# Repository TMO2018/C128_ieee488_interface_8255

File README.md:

# C128_ieee488_interface_8255
ieee488-Interface for the C128 using the expansions-port with PIA 8255 published in the 64er Sonderheft 10

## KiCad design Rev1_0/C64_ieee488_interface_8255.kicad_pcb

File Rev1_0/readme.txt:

Kicad 5.0.1

rev 1.0
- PCBWay
- Expansionsport- und ieee488-Platinenanschluss: beidseitig 45 Grad anfasen, 0,5mm tief

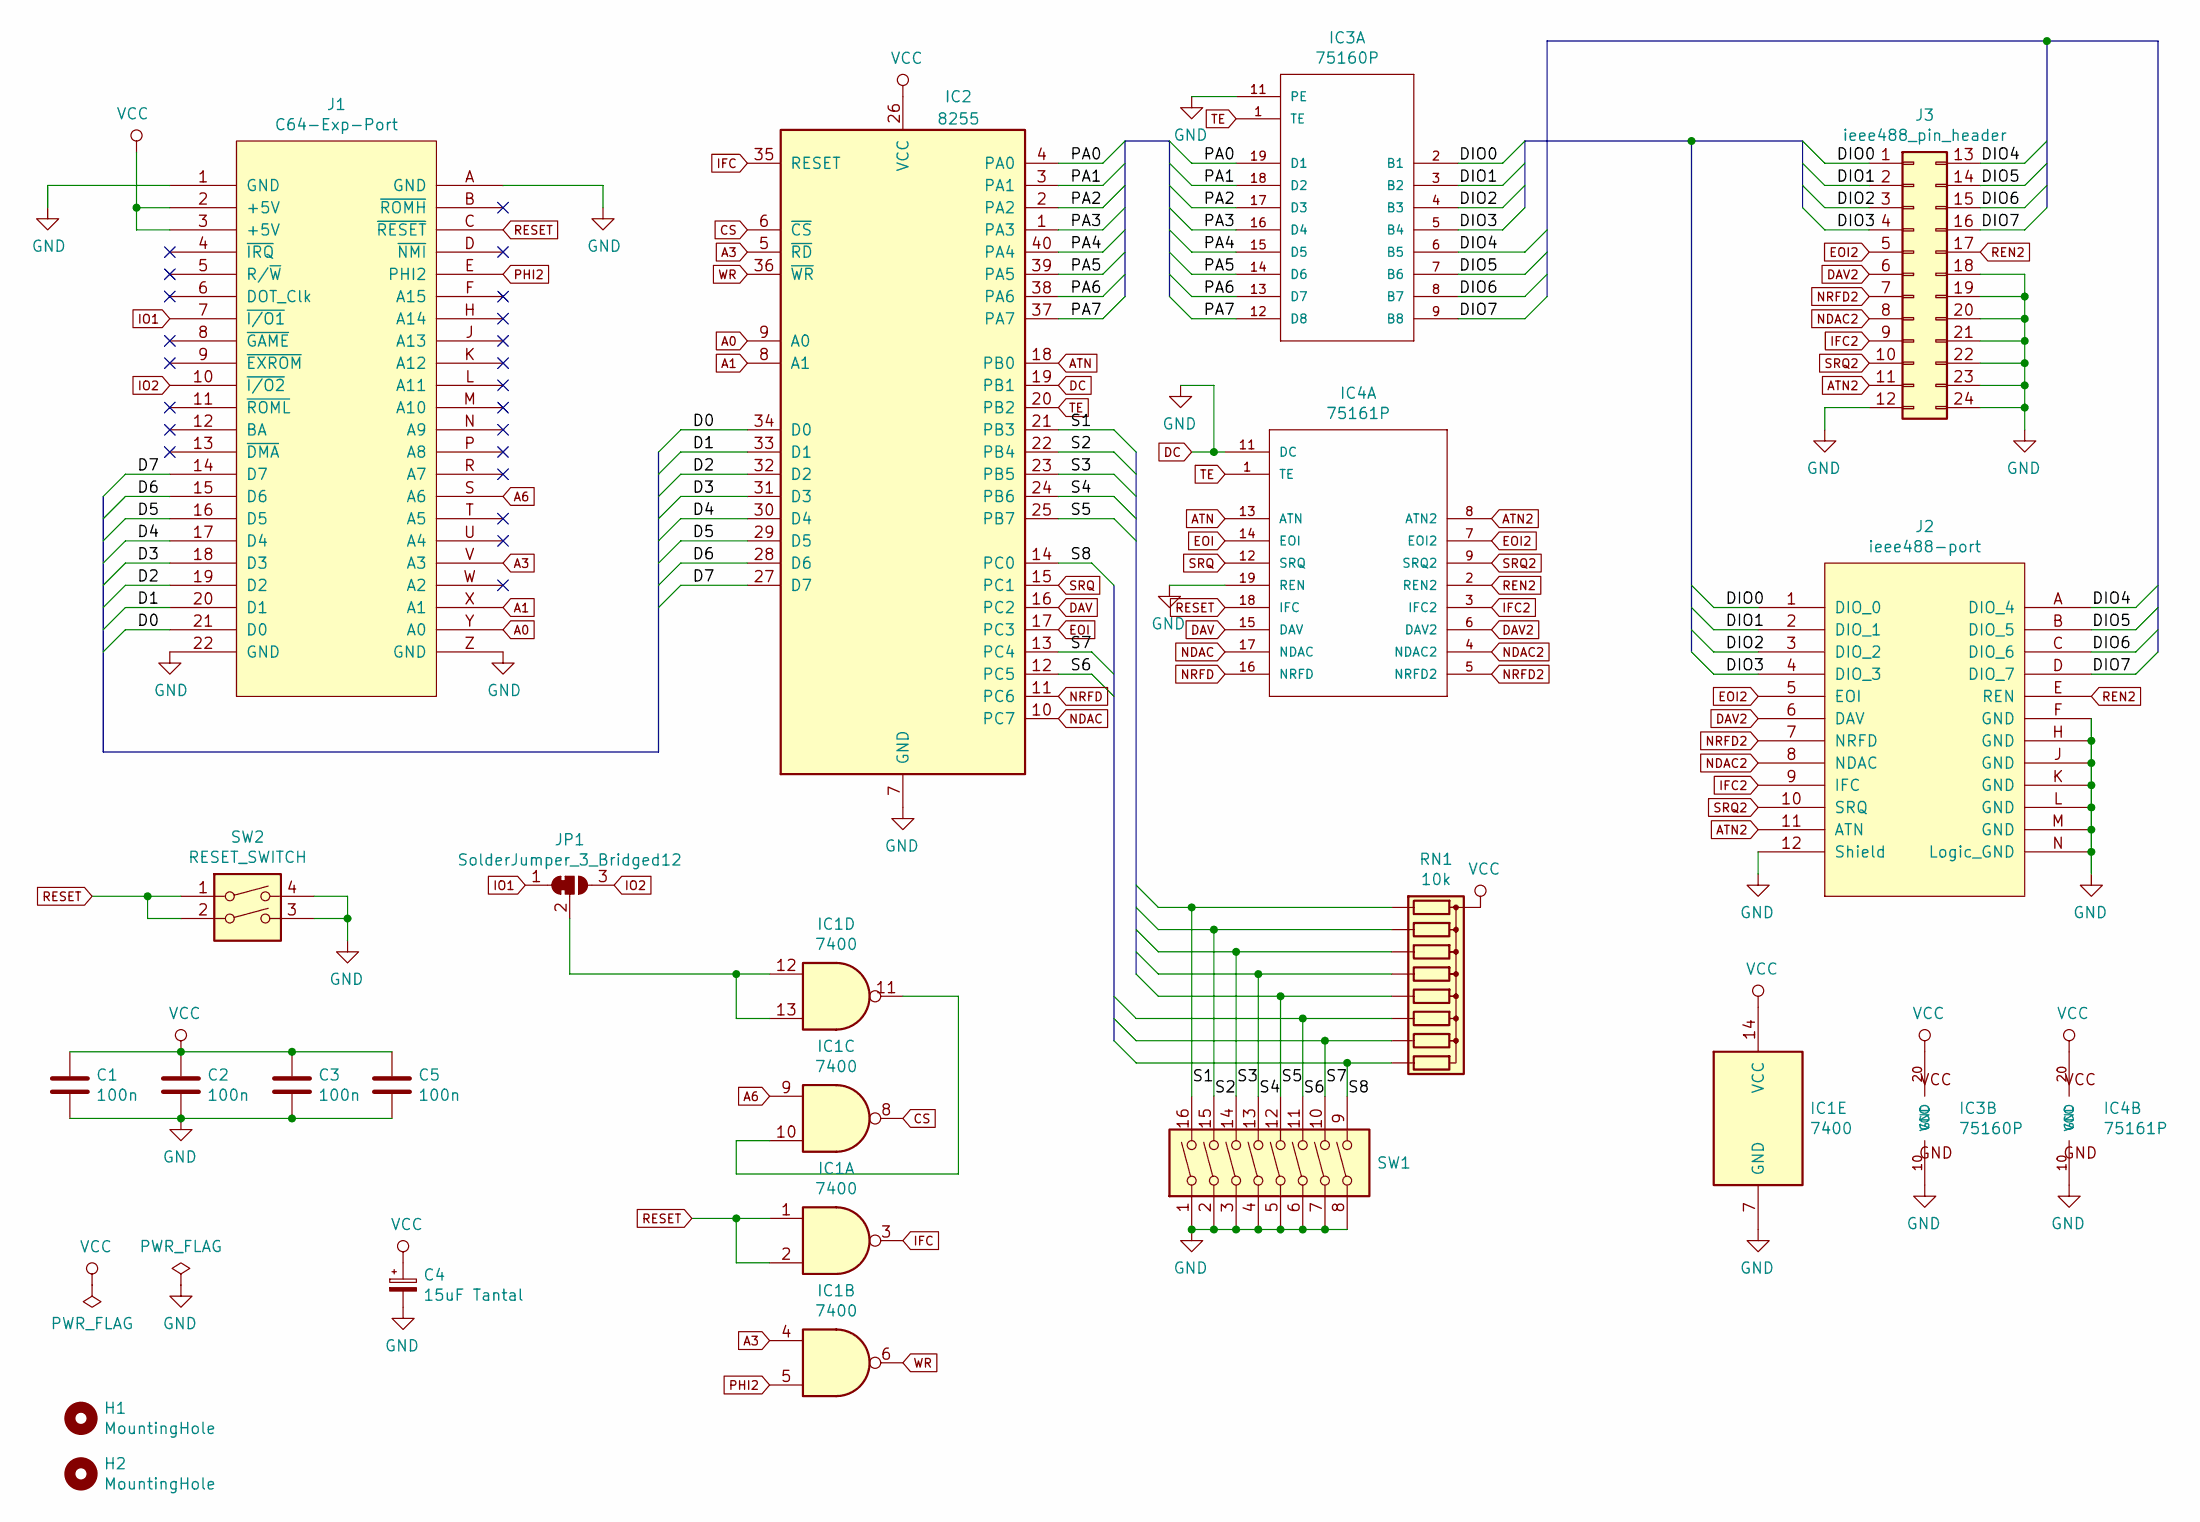
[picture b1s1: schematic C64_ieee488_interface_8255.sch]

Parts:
C1, C2, C3, C5: 100n; C_1206_HandSoldering
C4: 15uF Tantal; CP_Radial_D5.0mm_P2.50mm
H1, H2: MountingHole; MountingHole_3.2mm_M3
IC1: 7400; DIP-14_W7.62mm_LongPads
IC2: 8255; DIP-40_W15.24mm_LongPads
IC3: 75160P; DIP-20_W7.62mm_LongPads
IC4: 75161P; DIP-20_W7.62mm_LongPads
J1: C64-Exp-Port; C64-Cart
J2: ieee488-port; ieee488-Port
J3: ieee488_pin_header; Pin_Header_Straight_2x12_Pitch2.54mm_ieee488
JP1: SolderJumper_3_Bridged12; SolderJumper-3_P1.3mm_Bridged12_Pad1.0x1.5mm_NumberLabels
RN1: 10k; R_Array_SIP9
SW1: SW_DIP_x08; SW_DIP_x8_W7.62mm_Slide_LowProfile
SW2: RESET_SWITCH; PCB_PUSH

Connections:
/D0: IC2.34 (D0), J1.21 (D0)
/D1: IC2.33 (D1), J1.20 (D1)
/D2: IC2.32 (D2), J1.19 (D2)
/D3: IC2.31 (D3), J1.18 (D3)
/D4: IC2.30 (D4), J1.17 (D4)
/D5: IC2.29 (D5), J1.16 (D5)
/D6: IC2.28 (D6), J1.15 (D6)
/D7: IC2.27 (D7), J1.14 (D7)
/DIO0: IC3.2 (B1), J2.1 (DIO_0), J3.1
/DIO1: IC3.3 (B2), J2.2 (DIO_1), J3.2
/DIO2: IC3.4 (B3), J2.3 (DIO_2), J3.3
/DIO3: IC3.5 (B4), J2.4 (DIO_3), J3.4
/DIO4: IC3.6 (B5), J2.A (DIO_4), J3.13
/DIO5: IC3.7 (B6), J2.B (DIO_5), J3.14
/DIO6: IC3.8 (B7), J2.C (DIO_6), J3.15
/DIO7: IC3.9 (B8), J2.D (DIO_7), J3.16
/PA0: IC2.4 (PA0), IC3.19 (D1)
/PA1: IC2.3 (PA1), IC3.18 (D2)
/PA2: IC2.2 (PA2), IC3.17 (D3)
/PA3: IC2.1 (PA3), IC3.16 (D4)
/PA4: IC2.40 (PA4), IC3.15 (D5)
/PA5: IC2.39 (PA5), IC3.14 (D6)
/PA6: IC2.38 (PA6), IC3.13 (D7)
/PA7: IC2.37 (PA7), IC3.12 (D8)
/S1: IC2.21 (PB3), RN1.2 (R1), SW1.16
/S2: IC2.22 (PB4), RN1.3 (R2), SW1.15
/S3: IC2.23 (PB5), RN1.4 (R3), SW1.14
/S4: IC2.24 (PB6), RN1.5 (R4), SW1.13
/S5: IC2.25 (PB7), RN1.6 (R5), SW1.12
/S6: IC2.12 (PC5), RN1.7 (R6), SW1.11
/S7: IC2.13 (PC4), RN1.8 (R7), SW1.10
/S8: IC2.14 (PC0), RN1.9 (R8), SW1.9
A0: IC2.9 (A0), J1.Y (A0)
A1: IC2.8 (A1), J1.X (A1)
A3: IC1.4, IC2.5 (~RD~), J1.V (A3)
A6: IC1.9, J1.S (A6)
ATN: IC2.18 (PB0), IC4.13 (ATN)
ATN2: IC4.8 (ATN2), J2.11 (ATN), J3.11
CS: IC1.8, IC2.6 (~CS~)
DAV: IC2.16 (PC2), IC4.15 (DAV)
DAV2: IC4.6 (DAV2), J2.6 (DAV), J3.6
DC: C1.2, C2.2, C3.2, C4.2, C5.2, IC1.7 (GND), IC2.7 (GND), IC2.19 (PB1), IC3.10 (GND), IC3.11 (PE), IC4.10 (GND), IC4.11 (DC), IC4.19 (REN), J1.1 (GND), J1.22 (GND), J1.A (GND), J1.Z (GND), J2.12 (Shield), J2.F (GND), J2.H (GND), J2.J (GND), J2.K (GND), J2.L (GND), J2.M (GND), J2.N (Logic_GND), J3.12, J3.18, J3.19, J3.20, J3.21, J3.22, J3.23, J3.24, SW1.1, SW1.2, SW1.3, SW1.4, SW1.5, SW1.6, SW1.7, SW1.8, SW2.3, SW2.4
EOI: IC2.17 (PC3), IC4.14 (EOI)
EOI2: IC4.7 (EOI2), J2.5 (EOI), J3.5
IFC: IC1.3, IC2.35 (RESET)
IFC2: IC4.3 (IFC2), J2.9 (IFC), J3.9
IO1: J1.7 (~I/O1), JP1.1 (A)
IO2: J1.10 (~I/O2), JP1.3 (B)
NDAC: IC2.10 (PC7), IC4.17 (NDAC)
NDAC2: IC4.4 (NDAC2), J2.8 (NDAC), J3.8
NRFD: IC2.11 (PC6), IC4.16 (NRFD)
NRFD2: IC4.5 (NRFD2), J2.7 (NRFD), J3.7
unnamed: IC1.10, IC1.11
unnamed: IC1.12, IC1.13, JP1.2 (C)
PHI2: IC1.5, J1.E (PHI2)
REN2: IC4.2 (REN2), J2.E (REN), J3.17
RESET: IC1.1, IC1.2, IC4.18 (IFC), J1.C (~RESET), SW2.1, SW2.2
SRQ: IC2.15 (PC1), IC4.12 (SRQ)
SRQ2: IC4.9 (SRQ2), J2.10 (SRQ), J3.10
TE: IC2.20 (PB2), IC3.1 (TE), IC4.1 (TE)
VCC: C1.1, C2.1, C3.1, C4.1, C5.1, IC1.14 (VCC), IC2.26 (VCC), IC3.20 (VCC), IC4.20 (VCC), J1.2 (+5V), J1.3 (+5V), RN1.1 (common)
WR: IC1.6, IC2.36 (~WR~)

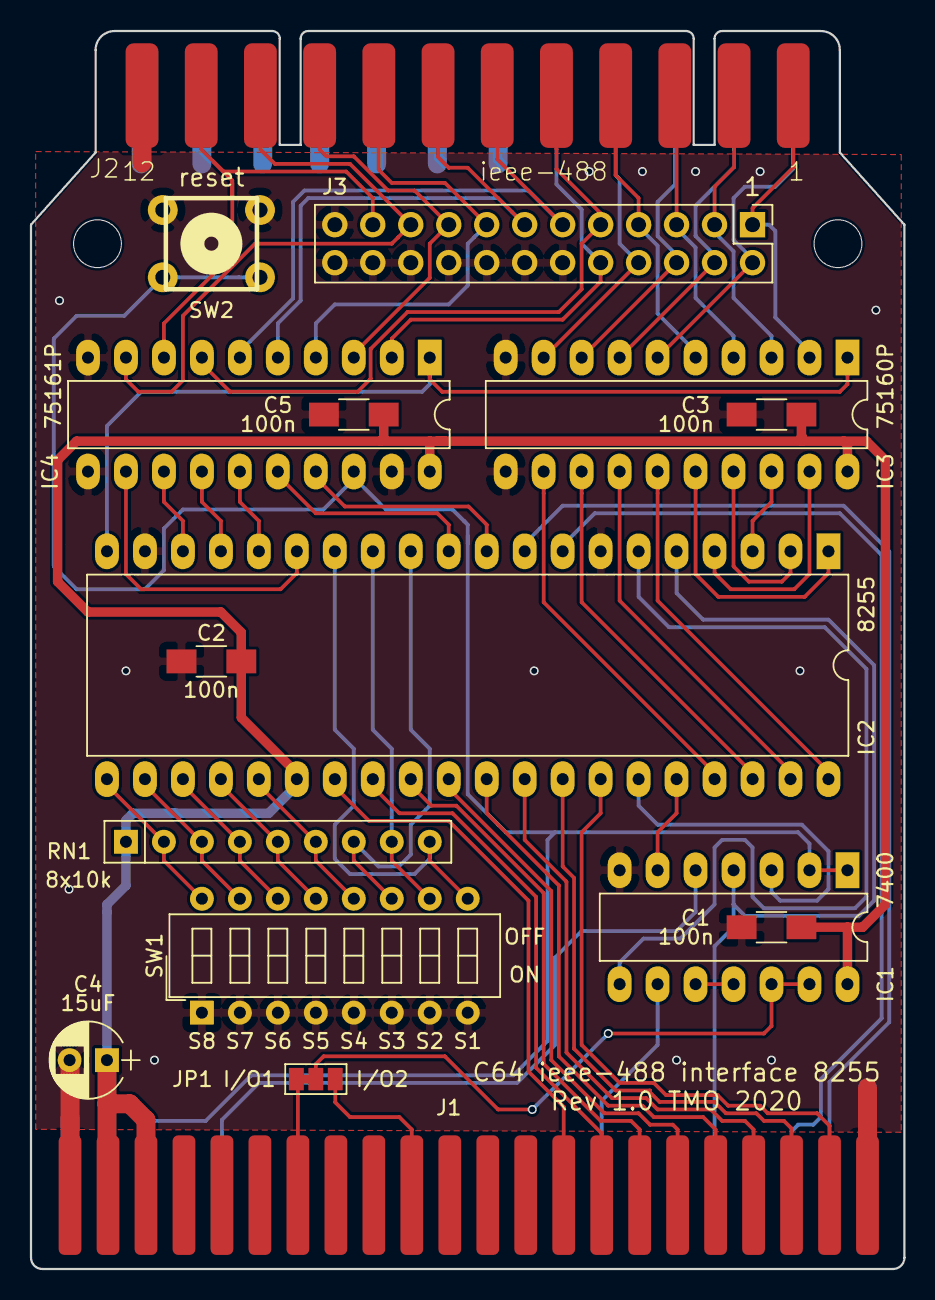
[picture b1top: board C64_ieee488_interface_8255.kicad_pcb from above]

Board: 2 copper layers, 58.4 x 82.8 mm, 18 parts (0 on the bottom side), 62 nets.

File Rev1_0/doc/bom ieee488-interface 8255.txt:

IC1 : SN7400 (DIL14 7,62mm)
IC2 : 8255 (DIL40 15,24mm)
IC3 : SN75160P (DIL20 7,62mm)
IC4 : SN75161P (DIL20 7,62mm)
C1,C2,C3,C5 : capacitor ceramic 100nF SMD 1206
C4 : capacitor electrolyt radial 15uF 16V D5.0 RM2.5
RN1 : resistor array SIP9 8x10k
SW1 : button switch DIP x8 W7.62mm
SW2 : push button print 6mm
J3 : pin header 2x12 straight RM2.54
